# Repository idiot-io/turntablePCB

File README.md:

# turntablePCB
a rotary encoder on a pcb

[https://wiki.idiot.io/pcbgreycode](https://wiki.idiot.io/pcbgraycode)

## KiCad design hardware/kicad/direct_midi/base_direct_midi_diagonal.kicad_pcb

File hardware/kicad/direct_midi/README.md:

# Direct RC + MIDI revision

Open `base_direct_midi.kicad_pro` to load the schematic, PCB, and local
footprint library for this revision. The historical artwork and its imported
KiCad board remain separate.

- All populated parts mount on `B.Cu`. The wheel's patterned face faces the
  clear `F.Cu` side of the base. The lenses point from the underside through
  the slot toward the wheel. All ten sensor centers and five mounting holes
  are unchanged. The slot has extra clearance at both ends for the inverted
  packages and still leaves the outer board outline unchanged.
- The Waveshare ESP32-S3-Zero and the 3.5 mm Type A MIDI OUT jack mount on the
  underside, with both connectors still facing the same board edge.
  U1 uses the v2 STEP model from [Waveshare's resources][waveshare] for 3D
  visualization; the solder-down footprint is unchanged.
- The board uses USB for power and native USB MIDI. TRS MIDI out sinks the
  receiver's current loop through Q1, a 2N7002 N-FET on the 5 V side; GPIO10
  drives its gate and R19 holds that gate low during reset. The switch inverts,
  so the UART TX polarity must be inverted. All ten optical inputs use direct
  RC readout.
- GPIO11 (`QUAD_A`, U11) and GPIO12 (`QUAD_B`, U12) read the two outer rings on
  the [100 mm wheel](../../wheel_quadrature_100mm.svg). Each ring has 128
  cycles; the quarter-cycle pattern offset gives 512 nominal counts per turn.
  These pins are not continuous logic-level outputs: firmware must charge,
  time and threshold the two RC channels before decoding quadrature.
- The jack footprint is CUI Devices `SJ-3523-SMT`. The local
  `QRE1113GR_OpticalSlot` footprint mirrors the lead pattern for lens-first
  assembly. Hand-solder these ten parts with the lenses inserted into the
  slot and the lead toes resting on the underside rails; do not place them
  lens-out for standard reflow. The pin-1 mark identifies the anode pad.
  These ten footprints intentionally have no stencil paste apertures.
- J1 sits at the edge because the plug enters from outside the board: the jack
  body ends 0.46 mm inside the outline and only the footprint's courtyard band
  crosses it, by 0.04 mm. The kicad-happy `PM-002` placement check reports that
  as an error: its edge-mount exemption has no audio-jack entry, and the PCB
  analyzer does not apply `.kicad-happy.json` suppressions (only the EMC and
  thermal analyzers do). Read it as a waiver, not as a defect.
- The curved routing is made of native KiCad tracks and circular arcs, not
  imported copper graphics. Ground uses the two GND pours and stitching vias
  instead of separate traces. The pours have thermal reliefs. This wired-only
  revision has no S3-Zero antenna keepout.

KiCad 10 DRC passes with no violations, unconnected items, or schematic parity
issues. The schematic ERC still flags the grounded emitter in each stock
QRE1113GR symbol.

Before fabrication, dry-fit an actual QRE1113GR and the jack on a routed
coupon. Check inverted lead overlap and solder access, the lens height and
slot corner radius, and that the jack's nominal 0.8 mm locating pegs stay
below the top of the 1.6 mm base. Set wheel spacing to clear the lenses and
mounting hardware through a full turn, then check stripe contrast and tune
the RC timing on the actual wheel. Verify that the TENSTAR clone matches
the Waveshare castellations and clears the carrier on its underside.

References: [Waveshare hardware resources][waveshare] and
[MIDI electrical specification][midi].

[waveshare]: https://docs.waveshare.com/ESP32-S3-Zero/Resources-And-Documents
[midi]: https://midi.org/5-pin-din-electrical-specs

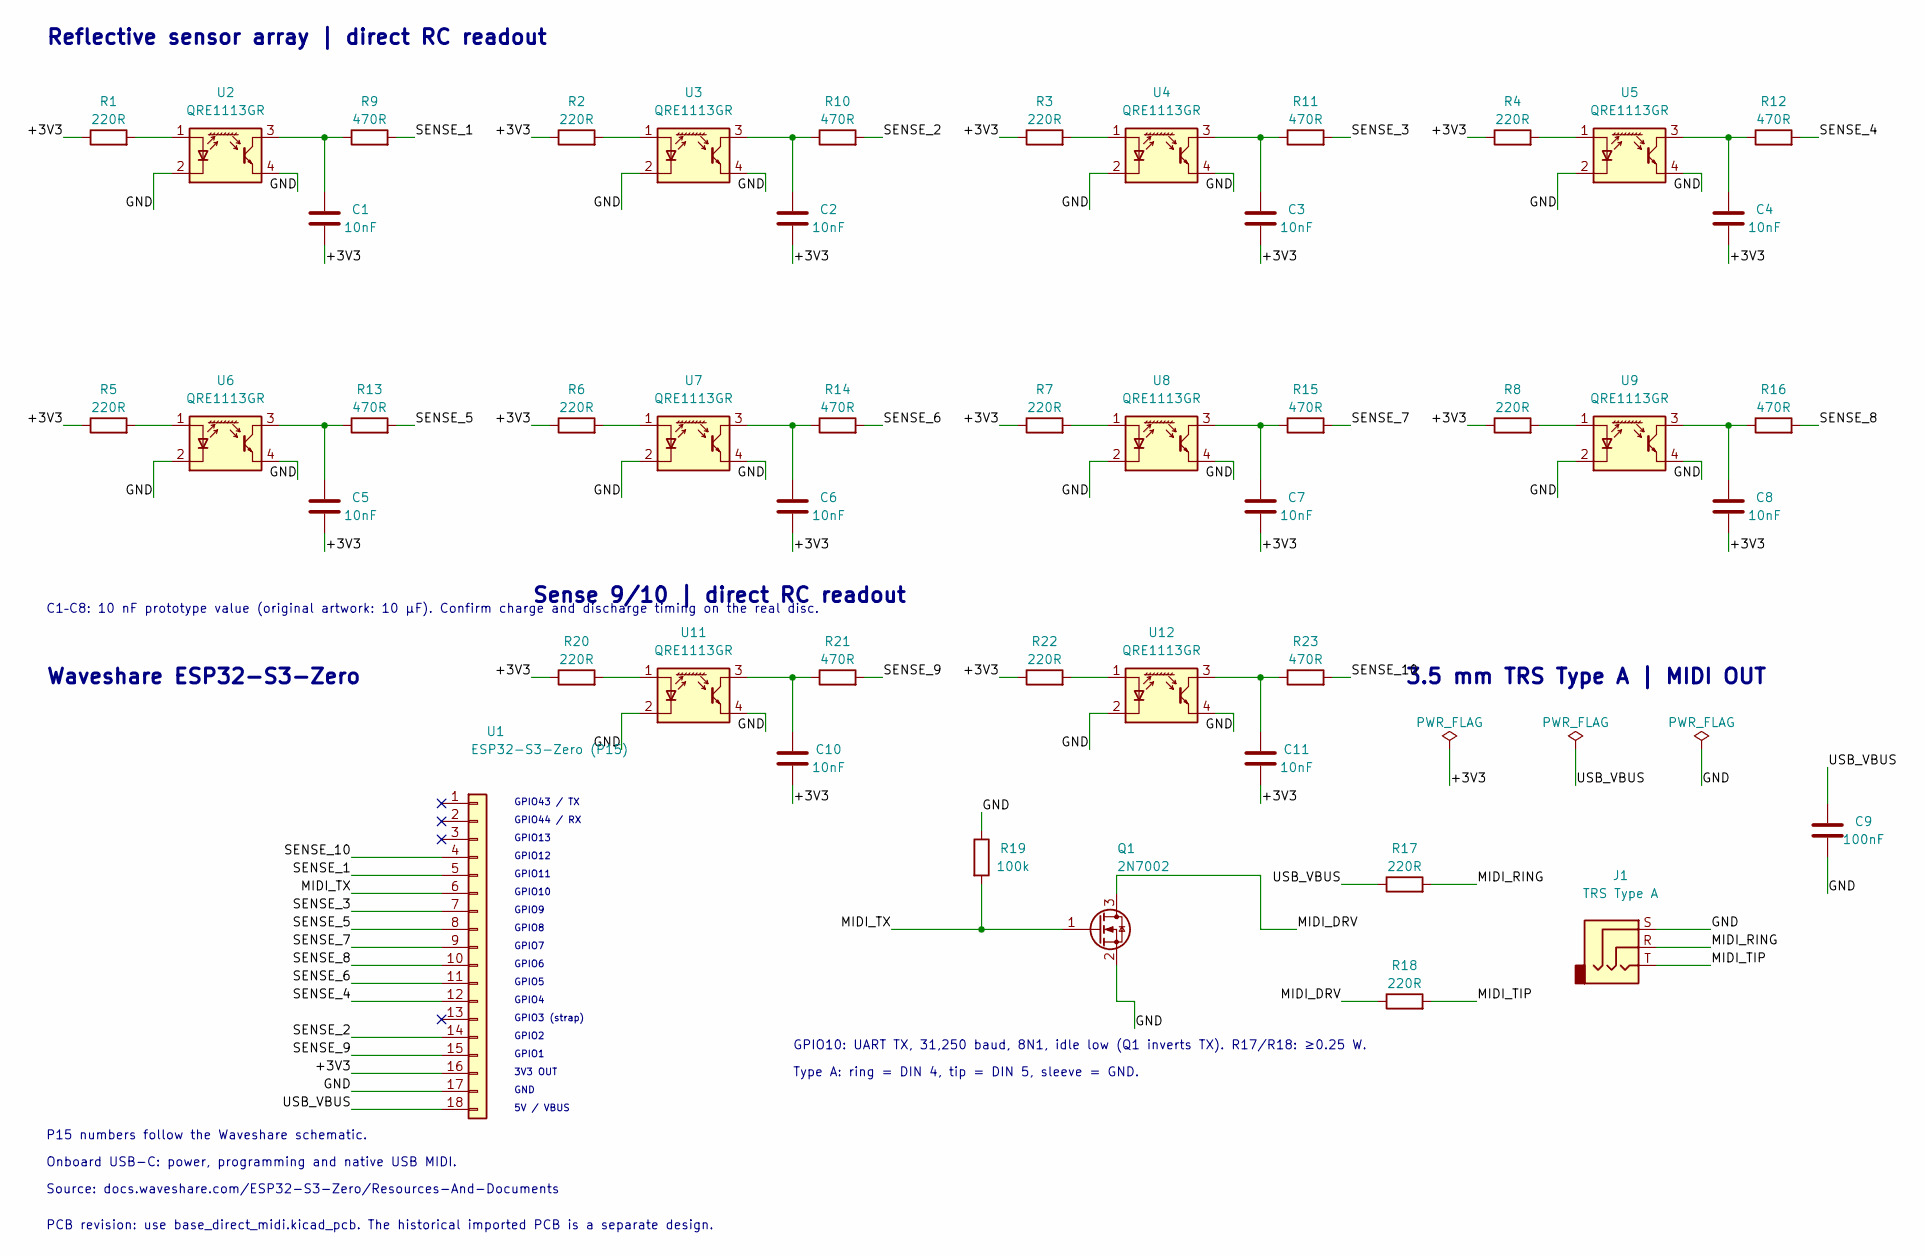
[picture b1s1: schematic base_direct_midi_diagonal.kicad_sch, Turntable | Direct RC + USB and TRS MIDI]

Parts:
C1, C2, C3, C4, C5, C6, C7, C8, C10, C11: 10nF; C_1206_3216Metric
C9: 100nF; C_0805_2012Metric
J1: TRS Type A; Jack_3.5mm_CUI_SJ-3523-SMT_Horizontal
Q1: 2N7002; SOT-23
R1, R2, R3, R4, R5, R6, R7, R8, R20, R22: 220R; R_0805_2012Metric
R9, R10, R11, R12, R13, R14, R15, R16, R21, R23: 470R; R_0805_2012Metric
R17, R18: 220R; R_1206_3216Metric
R19: 100k; R_0805_2012Metric
U1: ESP32-S3-Zero (P15); Waveshare_ESP32-S3-Zero_Castellated
U2, U3, U4, U5, U6, U7, U8, U9, U11, U12: QRE1113GR; QRE1113GR_OpticalSlot

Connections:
/+3V3: C1.2, C2.2, C3.2, C4.2, C5.2, C6.2, C7.2, C8.2, C10.2, C11.2, R1.1, R2.1, R3.1, R4.1, R5.1, R6.1, R7.1, R8.1, R20.1, R22.1, U1.16
/GND: C9.2, J1.S, Q1.2 (S), R19.1, U1.17, U2.2 (K), U2.4, U3.2 (K), U3.4, U4.2 (K), U4.4, U5.2 (K), U5.4, U6.2 (K), U6.4, U7.2 (K), U7.4, U8.2 (K), U8.4, U9.2 (K), U9.4, U11.2 (K), U11.4, U12.2 (K), U12.4
/MIDI_DRV: Q1.3 (D), R18.1
/MIDI_RING: J1.R, R17.2
/MIDI_TIP: J1.T, R18.2
/MIDI_TX: Q1.1 (G), R19.2, U1.6
/SENSE_1: R9.2, U1.5
/SENSE_2: R10.2, U1.14
/SENSE_3: R11.2, U1.7
/SENSE_4: R12.2, U1.12
/SENSE_5: R13.2, U1.8
/SENSE_6: R14.2, U1.11
/SENSE_7: R15.2, U1.9
/SENSE_8: R16.2, U1.10
/SENSE_9: R21.2, U1.15
/SENSE_10: R23.2, U1.4
/USB_VBUS: C9.1, R17.1, U1.18
unnamed: C1.1, R9.1, U2.3
unnamed: C2.1, R10.1, U3.3
unnamed: C3.1, R11.1, U4.3
unnamed: C4.1, R12.1, U5.3
unnamed: C5.1, R13.1, U6.3
unnamed: C6.1, R14.1, U7.3
unnamed: C7.1, R15.1, U8.3
unnamed: C8.1, R16.1, U9.3
unnamed: C10.1, R21.1, U11.3
unnamed: C11.1, R23.1, U12.3
unnamed: R1.2, U2.1 (A)
unnamed: R2.2, U3.1 (A)
unnamed: R3.2, U4.1 (A)
unnamed: R4.2, U5.1 (A)
unnamed: R5.2, U6.1 (A)
unnamed: R6.2, U7.1 (A)
unnamed: R7.2, U8.1 (A)
unnamed: R8.2, U9.1 (A)
unnamed: R20.2, U11.1 (A)
unnamed: R22.2, U12.1 (A)

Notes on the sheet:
GPIO2
GPIO10
GPIO5
3.5 mm TRS Type A | MIDI OUT
GPIO6
Sense 9/10 | direct RC readout
5V / VBUS
GPIO11
GPIO10: UART TX, 31,250 baud, 8N1, idle low (Q1 inverts TX). R17/R18: ≥0.25 W.
GPIO44 / RX
Onboard USB-C: power, programming and native USB MIDI.
GND
GPIO3 (strap)
GPIO4
GPIO9
GPIO12
GPIO7
Reflective sensor array | direct RC readout
GPIO1
GPIO13
GPIO8
PCB revision: use base_direct_midi.kicad_pcb. The historical imported PCB is a separate design.
P15 numbers follow the Waveshare schematic.
3V3 OUT
GPIO43 / TX
Type A: ring = DIN 4, tip = DIN 5, sleeve = GND.
Source: docs.waveshare.com/ESP32-S3-Zero/Resources-And-Documents
C1–C8: 10 nF prototype value (original artwork: 10 µF). Confirm charge and discharge timing on the real disc.
Waveshare ESP32-S3-Zero

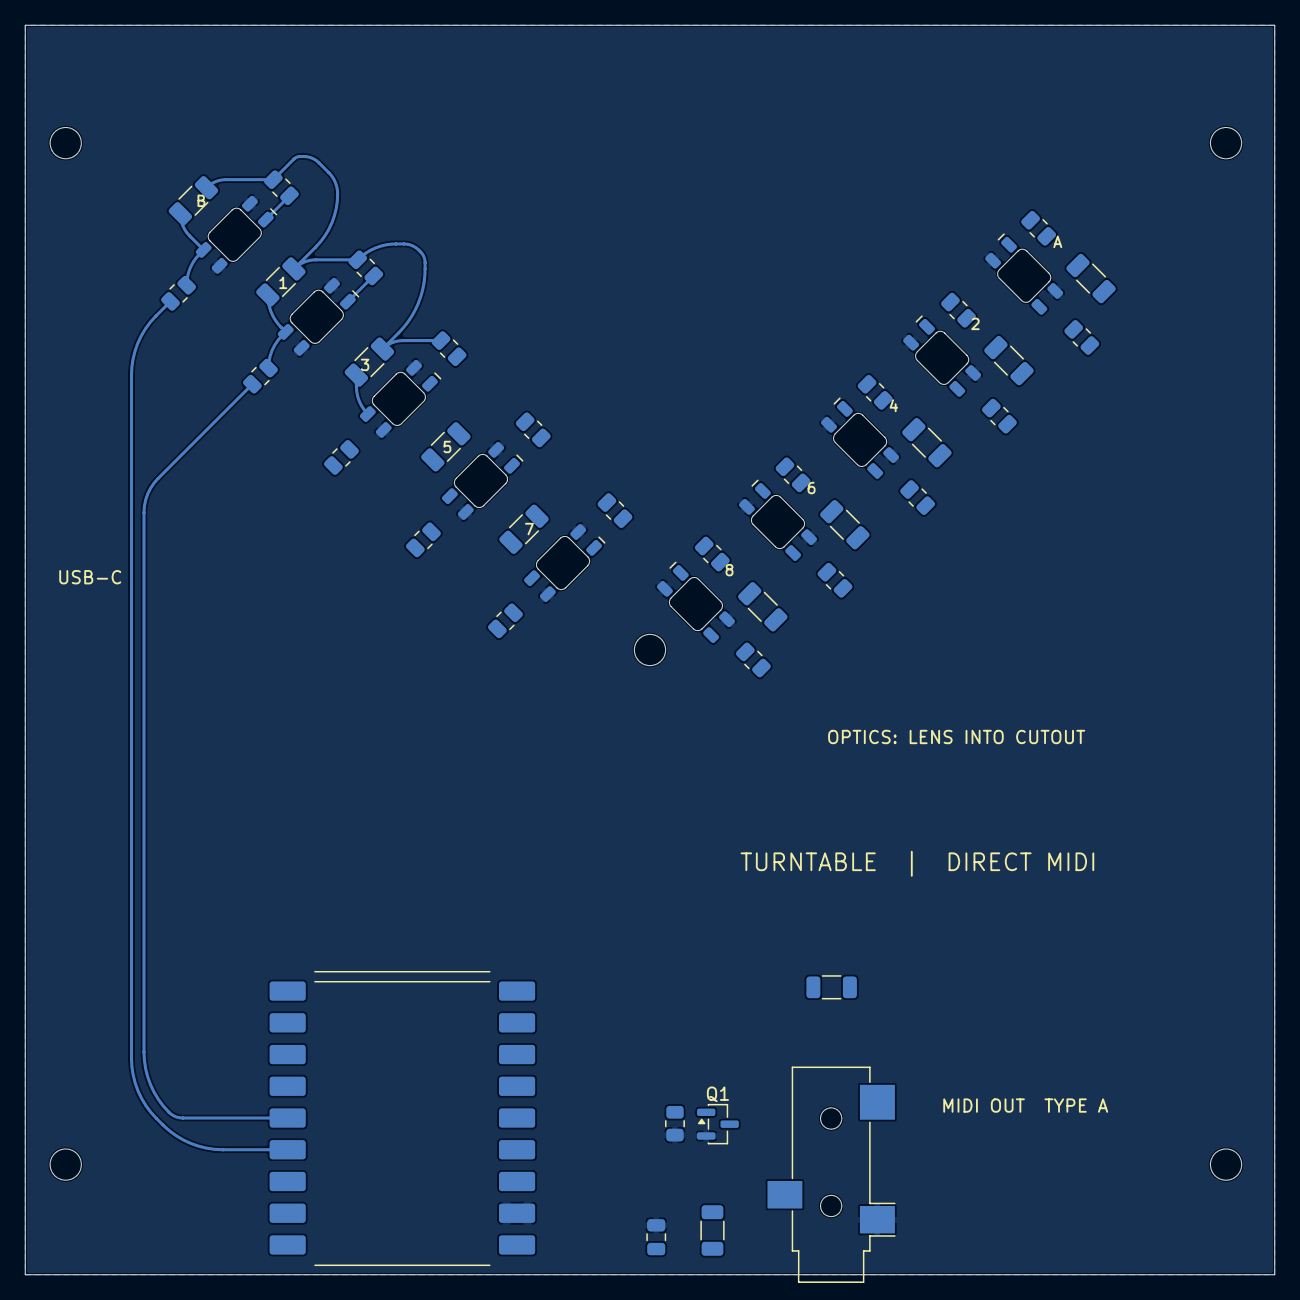
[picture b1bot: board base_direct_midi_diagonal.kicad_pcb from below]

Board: 2 copper layers, 100.0 x 100.0 mm, 52 parts (47 on the bottom side), 37 nets.

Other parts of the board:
H1, H2, H3, H4, H5: MountingHole_2.5mm

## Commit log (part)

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2018-07-19 board
2018-07-28 ignore
2019-01-06 ver01
2019-01-06 Update README.md
    better images... please
2019-01-07 release v01
2019-01-10 v1.2
2019-01-11 added mask pads, thank pcbway for noticing
2019-01-20 v1.3
2019-01-20 v1.33
2019-01-20 connected gorunds to emitter and Cathodes, moved copper to back of board
2019-01-20 now with circuit!
2019-01-20 now with circuit, and new base plot!
2019-01-21 side holes and silk ruler
2019-01-28 'fix flip'
2019-01-29 3.5mm slit, audioplug
2019-01-30 drill size for thruholes
2019-02-01 IC4051
2019-02-02 8bitwonder font, and need to flip IC
2019-02-02 flipped IC
2019-02-02 firmeware- first
2019-02-02 gitig
2019-02-07 renamed pcb dir
2019-02-07 new base, with IC4051
2019-02-08 flipped legend
2019-02-08 working code, based on pololu QTRSensors lib example
2019-02-10 working on i2c breakout
2019-02-10 added MCP23017
2019-02-11 i2c mux
2019-02-11 rev4
2019-02-11 working convert binary to int
2019-02-15 purr-data patch
2019-05-30 new code, works with rc-filter out
2019-05-30 table
2019-06-01 added gate select
2019-06-01 removed IC from baord
2019-06-01 base
